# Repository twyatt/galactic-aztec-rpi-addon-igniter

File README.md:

# About

Custom Raspberry Pi Add-on board used for launching the [Galactic Aztec] rocket to interface with the [Galactic Aztec Igniter Connector]. The board was designed to be stackable with other add-on boards via the designated [pin configuration].

Custom EagleCAD parts on this board can be found in the [SDSU Rocket Eagle Libraries].

## Wiring
The igniter and break wires that ran from the add-on board to the rocket's igniter were [CAT6 cables] that ran thru [RJ45 couplers] and followed the following [T-568B] wiring configurations:

### Igniter
| Pin | Color        | Function       |
|:---:|:------------:|:--------------:|
| 1   | Orange/White | Supply Voltage |
| 2   | Orange       | Ground         |
| 3   | Green/White  | Supply Voltage |
| 4   | Blue         | Ground         |
| 5   | Blue/White   | Supply Voltage |
| 6   | Green        | Ground         |
| 7   | Brown/White  | Supply Voltage |
| 8   | Brown        | Ground         |

### Break Wire
| Pin | Color        | Function       |
|:---:|:------------:|:--------------:|
| 1   | Orange/White | 3.3V           |
| 2   | Orange       | Signal         |
| 3   | Green/White  | 3.3V           |
| 4   | Blue         | Signal         |
| 5   | Blue/White   | 3.3V           |
| 6   | Green        | Signal         |
| 7   | Brown/White  | 3.3V           |
| 8   | Brown        | Signal         |

# Bill of Materials
| Qty | Description                          | Part Number         | Vendor   |
|:---:|--------------------------------------|--------------------:|----------|
| 1   | Header Stacking 2x20 Tall 23mm       | [1979]              | Adafruit |
| 2   | Diode 50V 1A PTH                     | [1N4001FSCT-ND]     | DigiKey  |
| 2   | Transistor NPN 40V 0.6A TO-92 PTH    | [2N5551TAFSTB-ND]   | DigiKey  |
| 3   | Jack RJ45 CAT5/CAT5e                 | [380-1046-ND]       | DigiKey  |
| 1   | LED Red Vf=1.8V If=2mA 0603          | [475-1195-2-ND]     | DigiKey  |
| 1   | Molex Mini Fit Jr. 4-pos Right Angle | [WM1352-ND]         | DigiKey  |
| 1   | LED Red Vf=2V If=20mA 0603           | [754-1359-1-ND]     | DigiKey  |
| 1   | Resistor 1.8kΩ 1/4W 1% 0603          | [P1.8KBYCT-ND]      | DigiKey  |
| 1   | Resistor 1.2kΩ 2W 1% 2512            | [A116034CT-ND]      | DigiKey  |
| 2   | Resistor 1k 1/4W 1% PTH              | [RNF14FTD1K00CT-ND] | DigiKey  |
| 1   | Header Female 1x6 0.1" Pitch         | [S7039-ND]          | DigiKey  |
| 2   | Relay 5V 5A SPST-NO (1 Form A)       | [Z945-ND]           | DigiKey  |

[Galactic Aztec]: http://rocket.sdsu.edu/rockets
[Galactic Aztec Igniter Connector]: https://github.com/twyatt/galactic-aztec-igniter-connector
[pin configuration]: https://docs.google.com/spreadsheets/d/1zGslKhH-ZteeA8sbbTjQlF-Neb-wJ3quIlFH6I8Cvgs/edit?usp=sharing
[CAT6 cables]: http://amzn.com/B00DUYDFVY
[RJ45 connector pin configuration]: https://docs.google.com/spreadsheets/d/1SQShVjZaio6u5dARqMazgQztgd2wGieyxO2AVLGVz4Q/edit?usp=sharing
[RJ45 couplers]: http://amzn.com/B00GE1DHRC
[SDSU Rocket Eagle Libraries]: https://github.com/twyatt/SDSURocket-Eagle-Libraries
[T-568B]: https://en.wikipedia.org/wiki/TIA/EIA-568#Wiring
[1979]: http://www.adafruit.com/products/1979
[1N4001FSCT-ND]: http://www.digikey.com/product-detail/en/1N4001/1N4001FSCT-ND/1532742
[2N5551TAFSTB-ND]: http://www.digikey.com/product-detail/en/2N5551TA/2N5551TAFSTB-ND/973959
[380-1046-ND]: http://www.digikey.com/product-detail/en/SS-7188-NF/380-1046-ND/388308
[475-1195-2-ND]: http://www.digikey.com/product-detail/en/LS%20L29K-H1J2-1-Z/475-1195-1-ND/810356
[WM1352-ND]: http://www.digikey.com/product-search/en?x=0&y=0&lang=en&site=us&keywords=538-39-30-1040
[754-1359-1-ND]: http://www.digikey.com/product-detail/en/APG1608SURKC%2FT/754-1359-1-ND/1919171
[P1.8KBYCT-ND]: http://www.digikey.com/product-detail/en/ERJ-PA3F1801V/P1.8KBYCT-ND/5036145
[A116034CT-ND]: http://www.digikey.com/product-detail/en/5-2176070-1/A116034CT-ND/4280086
[RNF14FTD1K00CT-ND]: http://www.digikey.com/product-detail/en/RNF14FTD1K00/RNF14FTD1K00CT-ND/1975018
[S7039-ND]: http://www.digikey.com/product-detail/en/PPPC061LFBN-RC/S7039-ND/810178
[Z945-ND]: http://www.digikey.com/product-detail/en/G6B-1114P-US-DC5/Z945-ND/148724

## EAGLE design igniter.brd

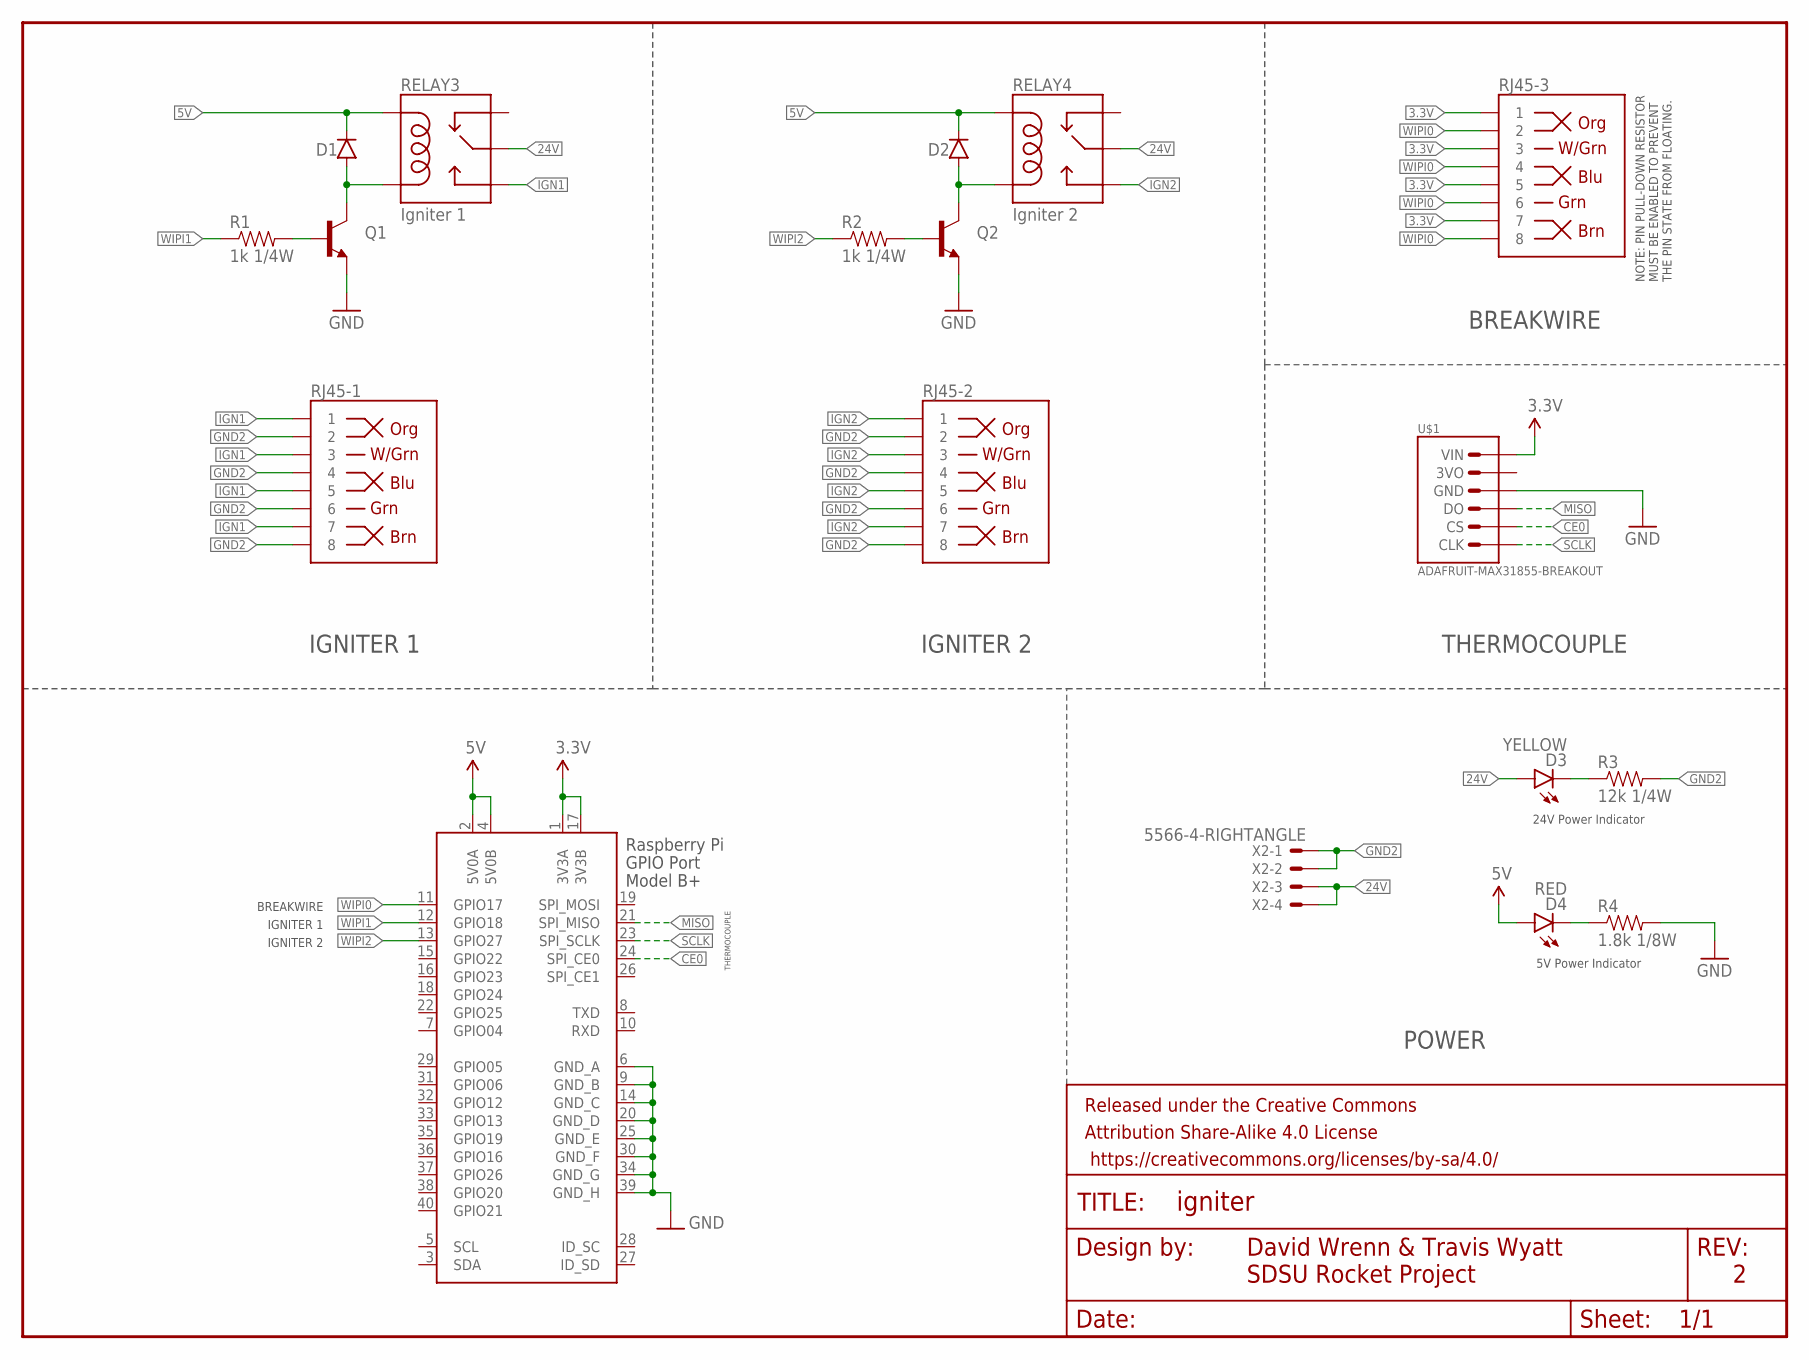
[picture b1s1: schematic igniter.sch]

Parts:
D1, D2: DIODEPTH; DIODE-1N4001
D3: YELLOW; LED-0603
D4: RED; LED-0603
FRAME1: FRAME-LETTER; CREATIVE_COMMONS
Q1, Q2: TRANSISTOR_NPNP2N2222A; TO-92
R1, R2: 1k 1/4W; AXIAL-0.3
R3: 12k 1/4W; 0603-RES
R4: 1.8k 1/8W; 0603-RES
RELAY3: Igniter 1; RELAY-G5Q
RELAY4: Igniter 2; RELAY-G5Q
RJ45-1, RJ45-2, RJ45-3: RJ45-8PTH; RJ45-8
U$1: ADAFRUIT-MAX31855-BREAKOUT; ADAFRUIT-MAX31855
X1: RASPI_BOARD_B+#_H; RASPI_BOARD_B+HAT
X2: 5566-4-RIGHTANGLE; 5566-4

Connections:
3.3V: RJ45-3.1, RJ45-3.3, RJ45-3.5, RJ45-3.7, U$1.VIN, X1.1 (3V3A), X1.17 (3V3B)
5V: D1.C, D2.C, D4.A, RELAY3.5 (COIL1), RELAY4.5 (COIL1), X1.2 (5V0A), X1.4 (5V0B)
24V: D3.A, RELAY3.2 (MAIN), RELAY4.2 (MAIN), X2.3, X2.4
CE0: U$1.CS, X1.24 (SPI_CE0)
GND: Q1.3 (E), Q2.3 (E), R4.2, U$1.GND, X1.6 (GND_A), X1.9 (GND_B), X1.14 (GND_C), X1.20 (GND_D), X1.25 (GND_E), X1.30 (GND_F), X1.34 (GND_G), X1.39 (GND_H)
GND2: R3.2, RJ45-1.2, RJ45-1.4, RJ45-1.6, RJ45-1.8, RJ45-2.2, RJ45-2.4, RJ45-2.6, RJ45-2.8, X2.1, X2.2
IGN1: RELAY3.3 (NO), RJ45-1.1, RJ45-1.3, RJ45-1.5, RJ45-1.7
IGN2: RELAY4.3 (NO), RJ45-2.1, RJ45-2.3, RJ45-2.5, RJ45-2.7
MISO: U$1.DO, X1.21 (SPI_MISO)
unnamed: Q1.2 (B), R1.P$2 (2)
unnamed: D1.A, Q1.1 (C), RELAY3.1 (COIL2)
unnamed: D3.C, R3.1
unnamed: D4.C, R4.1
unnamed: Q2.2 (B), R2.P$2 (2)
unnamed: D2.A, Q2.1 (C), RELAY4.1 (COIL2)
SCLK: U$1.CLK, X1.23 (SPI_SCLK)
WIPI0: RJ45-3.2, RJ45-3.4, RJ45-3.6, RJ45-3.8, X1.11 (GPIO17)
WIPI1: R1.P$1 (1), X1.12 (GPIO18)
WIPI2: R2.P$1 (1), X1.13 (GPIO27)

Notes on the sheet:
IGNITER 1
IGNITER 2
BREAKWIRE
POWER
THERMOCOUPLE
NOTE: PIN PULL-DOWN RESISTOR MUST BE ENABLED TO PREVENT THE PIN STATE FROM FLOATING.
David Wrenn & Travis Wyatt
SDSU Rocket Project
24V Power Indicator
5V Power Indicator

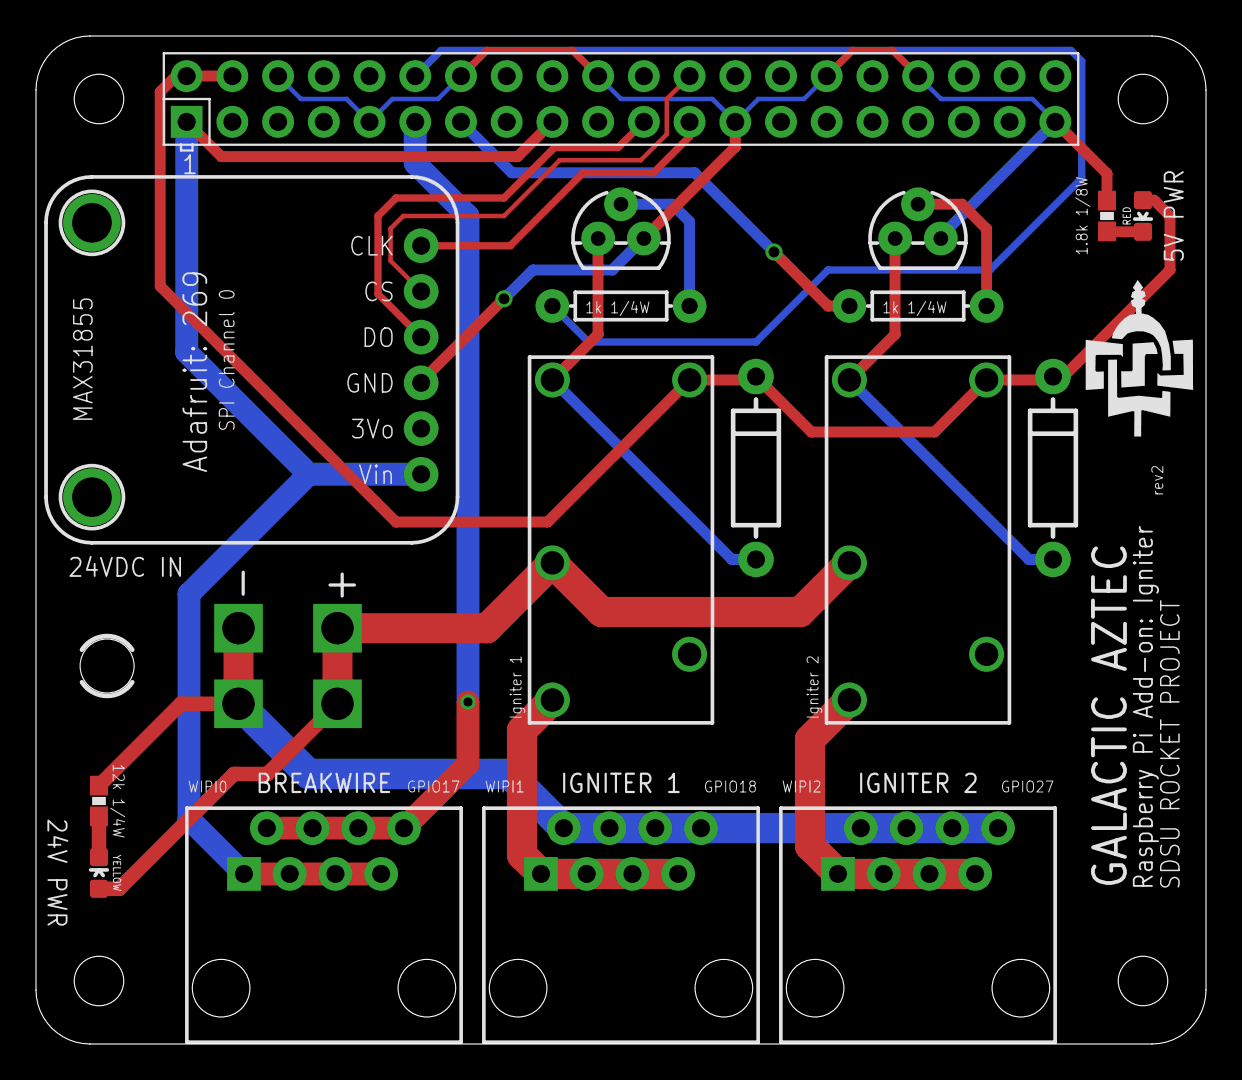
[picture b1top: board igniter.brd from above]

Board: 2 copper layers, 65.0 x 56.0 mm, 19 parts (0 on the bottom side), 19 nets.

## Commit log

2015-07-18 Initial commit.
2015-07-21 Power connector and resistor updates. Added PCB images (generated by OSHPark). Added README.md.
2015-07-29 README.md updates.

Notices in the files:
parts and their libraries:
SparkFun-DiscreteSemi: Licensing: Creative Commons ShareAlike 4.0 International - https://creativecommons.org/licenses/by-sa/4.0
SparkFun-Aesthetics: Released under the Creative Commons Attribution Share-Alike 4.0 License
SparkFun-Aesthetics: https://creativecommons.org/licenses/by-sa/4.0
